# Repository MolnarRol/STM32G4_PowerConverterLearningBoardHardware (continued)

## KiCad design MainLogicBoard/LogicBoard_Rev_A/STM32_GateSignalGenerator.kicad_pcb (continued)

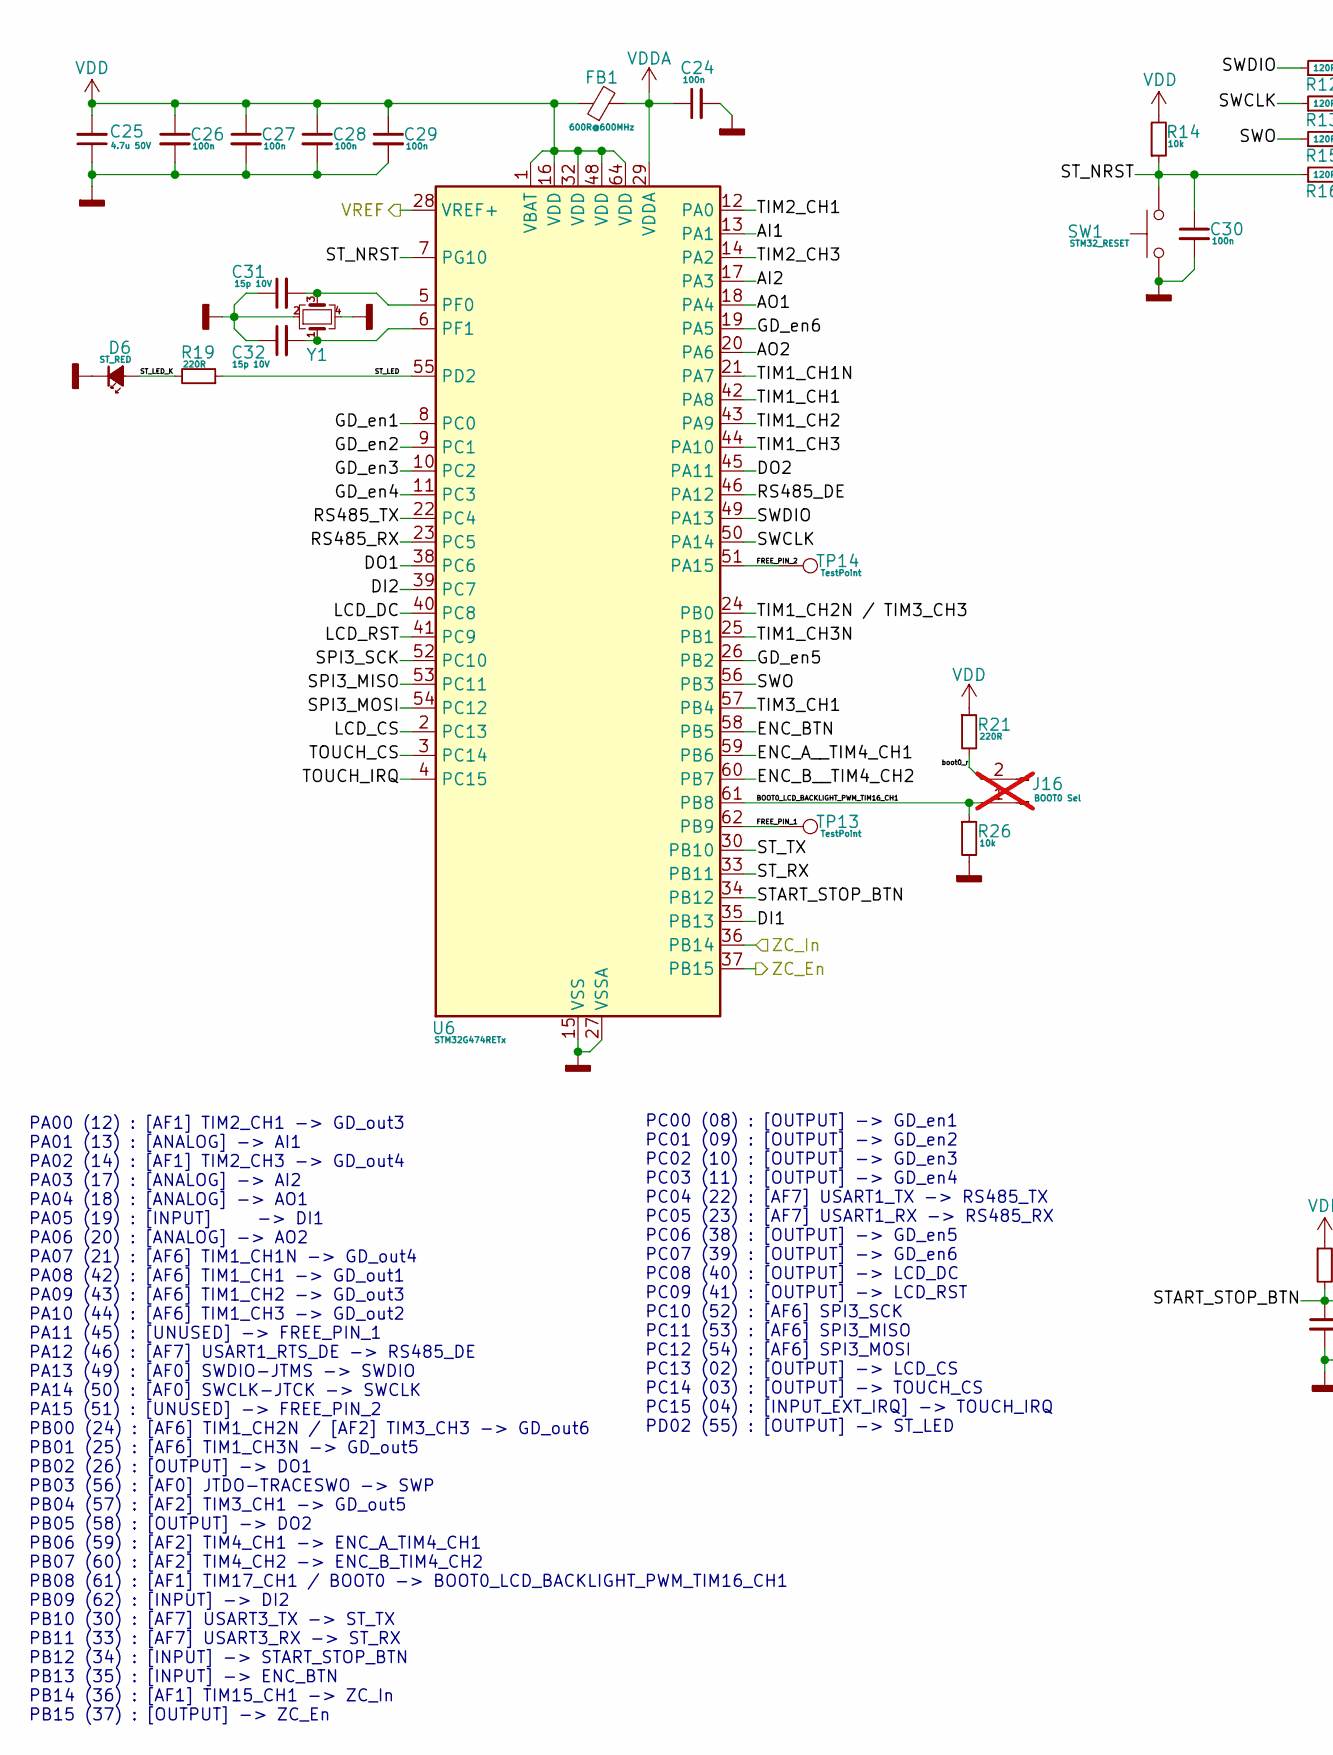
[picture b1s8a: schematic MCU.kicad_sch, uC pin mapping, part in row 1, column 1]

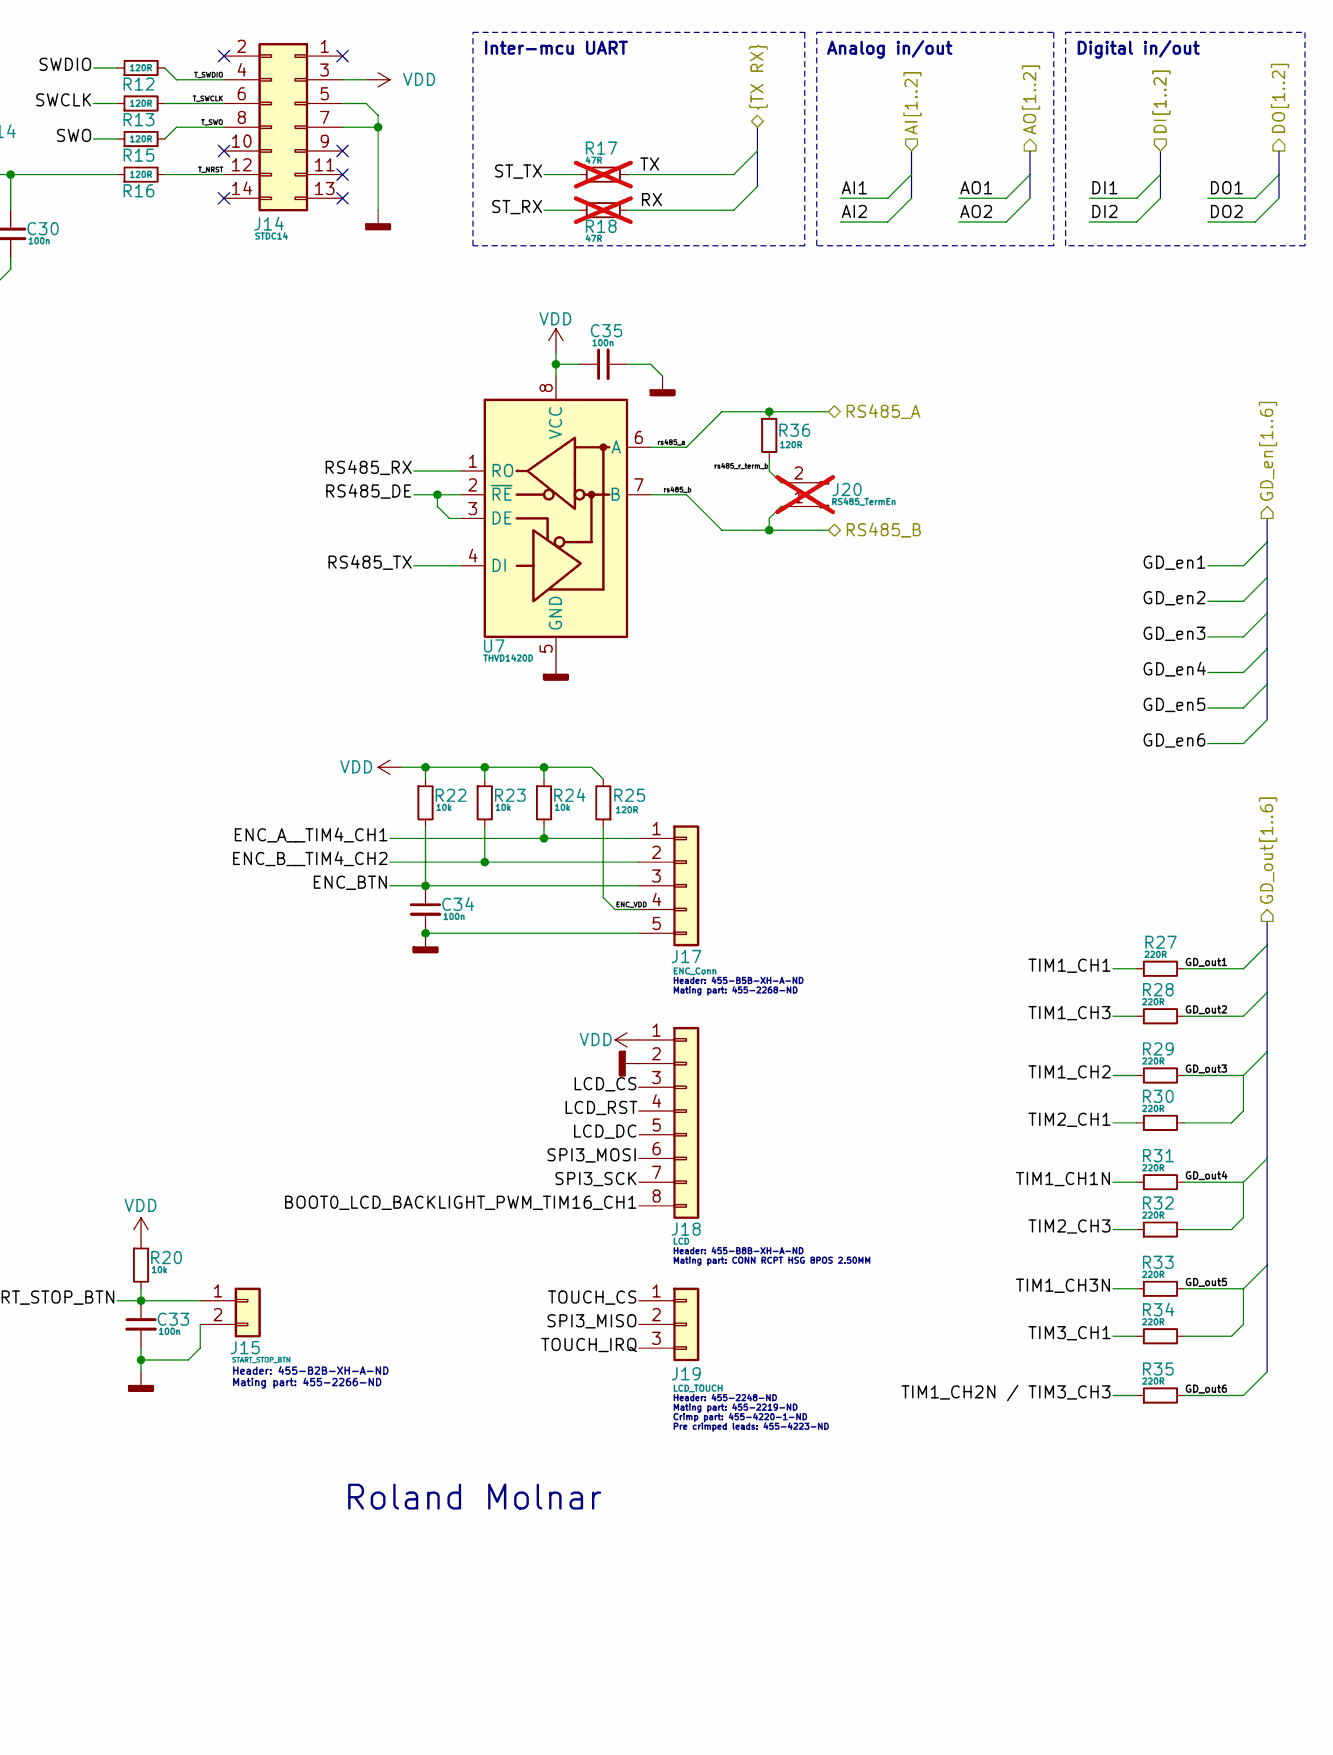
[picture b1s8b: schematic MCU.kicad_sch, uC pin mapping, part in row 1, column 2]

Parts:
C24, C30, C33, C34, C35: 100n; C_0805_2012Metric; Manufacturer PN C0805C104K5RAC7411; DigiKey PN 399-C0805C104K5RAC7210CT-ND
C25: 4.7u 50V; C_1206_3216Metric; Manufacturer PN GRM31CR71H475KA12L; DigiKey PN 490-6521-1-ND
C26, C27, C28, C29: 100n; C_0603_1608Metric; Manufacturer PN 06035C104JAT2A; DigiKey PN 478-KGM15BR71H104JTCT-ND
C31, C32: 15p 10V; C_0603_1608Metric; Manufacturer PN C0603C150M8GACTU; DigiKey PN 399-C0603C150M8GACTUCT-ND
D6: ST_RED; LED_0805_2012Metric; Manufacturer PN LTST-C171KRKT; DigiKey PN 160-1427-1-ND
FB1: 600R@600MHz; R_0805_2012Metric; Manufacturer PN BLM21HE122SN1L; DigiKey PN 490-BLM21HE122SN1LCT-ND
J14: STDC14; SAMTEC_FTSH-107-01-L-DV-K-A; Manufacturer PN SAMTEC_FTSH-107-01-L-DV-K-A; DigiKey PN FTSH-107-01-L-DV-K-A-ND
J15: START_STOP_BTN; JST_XH_B2B-XH-A_1x02_P2.50mm_Vertical; Manufacturer PN B2B-XH-A; DigiKey PN 455-B2B-XH-A-ND
J16: BOOT0 Sel; PinHeader_1x02_P2.54mm_Vertical; not fitted
J17: ENC_Conn; JST_XH_B5B-XH-A_1x05_P2.50mm_Vertical; Manufacturer PN B5B-XH-A; DigiKey PN 455-B5B-XH-A-ND
J18: LCD; JST_XH_B8B-XH-A_1x08_P2.50mm_Vertical; Manufacturer PN B8B-XH-A; DigiKey PN 455-B8B-XH-A-ND
J19: LCD_TOUCH; JST_XH_B3B-XH-A_1x03_P2.50mm_Vertical; Manufacturer PN B3B-XH-A; DigiKey PN 455-2248-ND
J20: RS485_TermEn; PinHeader_1x02_P2.54mm_Vertical; not fitted
R12, R13, R15, R16, R25: 120R; R_0603_1608Metric; Manufacturer PN AC0603FR-07120RL; DigiKey PN YAG3563CT-ND
R14, R20, R22, R23, R24, R26: 10k; R_0805_2012Metric; Manufacturer PN RT0805DRD0710KL; DigiKey PN 311-2699-1-ND
R17, R18: 47R; R_0603_1608Metric; not fitted
R19, R21, R27, R28, R29, R30, R31, R32, R33, R34, R35: 220R; R_0805_2012Metric; Manufacturer PN RC0805FR-07220RL; DigiKey PN 311-220CRCT-ND
R36: 120R; R_0805_2012Metric; Manufacturer PN RC0805FR-07120RL; DigiKey PN 311-120CRCT-ND
SW1: STM32_RESET; SW_SPST_PTS647_Sx38; Manufacturer PN PTS647SN50SMTR2 LFS; DigiKey PN PTS647SN50SMTR2LFSCT-ND
TP13, TP14: TestPoint; TestPoint_Pad_D1.5mm
U6: STM32G474RETx; LQFP-64_10x10mm_P0.5mm; Manufacturer PN STM32G474RET6; DigiKey PN 497-STM32G474RET6-ND
U7: THVD1420D; SOIC-8_3.9x4.9mm_P1.27mm; Manufacturer PN THVD1420DR; DigiKey PN 296-THVD1420DRCT-ND
Y1: FA-128 24.0000MF10Z-W3; Crystal_SMD_SeikoEpson_FA128-4Pin_2.0x1.6mm; Manufacturer PN FA-128 24.0000MF10Z-W3; DigiKey PN SER3678CT-ND

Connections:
/AnalogInterface/AI1: U6.13 (PA1); also elsewhere on the board
/AnalogInterface/AI2: U6.17 (PA3); also elsewhere on the board
/AnalogInterface/AO1: U6.18 (PA4); also elsewhere on the board
/AnalogInterface/AO2: U6.20 (PA6); also elsewhere on the board
/AnalogInterface/VREF: U6.28 (VREF+); also elsewhere on the board
/DigitalInterface/DI1: U6.35 (PB13); also elsewhere on the board
/DigitalInterface/DI2: U6.39 (PC7); also elsewhere on the board
/DigitalInterface/DO1: U6.38 (PC6); also elsewhere on the board
/DigitalInterface/DO2: U6.45 (PA11); also elsewhere on the board
/Gate driver connectors/GD_en1: U6.8 (PC0); also elsewhere on the board
/Gate driver connectors/GD_en2: U6.9 (PC1); also elsewhere on the board
/Gate driver connectors/GD_en3: U6.10 (PC2); also elsewhere on the board
/Gate driver connectors/GD_en4: U6.11 (PC3); also elsewhere on the board
/Gate driver connectors/GD_en5: U6.26 (PB2); also elsewhere on the board
/Gate driver connectors/GD_en6: U6.19 (PA5); also elsewhere on the board
/Gate driver connectors/GD_out1: R27.2; also elsewhere on the board
/Gate driver connectors/GD_out2: R28.2; also elsewhere on the board
/Gate driver connectors/GD_out3: R29.2, R30.2; also elsewhere on the board
/Gate driver connectors/GD_out4: R31.2, R32.2; also elsewhere on the board
/Gate driver connectors/GD_out5: R33.2, R34.2; also elsewhere on the board
/Gate driver connectors/GD_out6: R35.2; also elsewhere on the board
/MCU/BOOT0_LCD_BACKLIGHT_PWM_TIM16_CH1: J16.1, J18.8, R26.1, U6.61 (PB8)
/MCU/ENC_A__TIM4_CH1: J17.1, R24.2, U6.59 (PB6)
/MCU/ENC_BTN: C34.1, J17.3, R22.2, U6.58 (PB5)
/MCU/ENC_B__TIM4_CH2: J17.2, R23.2, U6.60 (PB7)
/MCU/ENC_VDD: J17.4, R25.1
/MCU/FREE_PIN_1: TP13.1, U6.62 (PB9)
/MCU/FREE_PIN_2: TP14.1, U6.51 (PA15)
/MCU/LCD_CS: J18.3, U6.2 (PC13)
/MCU/LCD_DC: J18.5, U6.40 (PC8)
/MCU/LCD_RST: J18.4, U6.41 (PC9)
/MCU/RS485_DE: U6.46 (PA12), U7.2 (~RE), U7.3 (DE)
/MCU/RS485_RX: U6.23 (PC5), U7.1 (RO)
/MCU/RS485_TX: U6.22 (PC4), U7.4 (DI)
/MCU/SPI3_MISO: J19.2, U6.53 (PC11)
/MCU/SPI3_MOSI: J18.6, U6.54 (PC12)
/MCU/SPI3_SCK: J18.7, U6.52 (PC10)
/MCU/START_STOP_BTN: C33.1, J15.1, R20.2, U6.34 (PB12)
/MCU/ST_LED: R19.1, U6.55 (PD2)
/MCU/ST_LED_K: D6.2 (A), R19.2
/MCU/ST_NRST: C30.1, R14.1, R16.1, SW1.2, U6.7 (PG10)
/MCU/ST_RX: R18.1, U6.33 (PB11)
/MCU/ST_TX: R17.1, U6.30 (PB10)
/MCU/SWCLK: R13.1, U6.50 (PA14)
/MCU/SWDIO: R12.1, U6.49 (PA13)
/MCU/SWO: R15.1, U6.56 (PB3)
/MCU/TIM1_CH1: R27.1, U6.42 (PA8)
/MCU/TIM1_CH1N: R31.1, U6.21 (PA7)
/MCU/TIM1_CH2: R29.1, U6.43 (PA9)
/MCU/TIM1_CH2N / TIM3_CH3: R35.1, U6.24 (PB0)
/MCU/TIM1_CH3: R28.1, U6.44 (PA10)
/MCU/TIM1_CH3N: R33.1, U6.25 (PB1)
/MCU/TIM2_CH1: R30.1, U6.12 (PA0)
/MCU/TIM2_CH3: R32.1, U6.14 (PA2)
/MCU/TIM3_CH1: R34.1, U6.57 (PB4)
/MCU/TOUCH_CS: J19.1, U6.3 (PC14)
/MCU/TOUCH_IRQ: J19.3, U6.4 (PC15)
/MCU/T_NRST: J14.12, R16.2
/MCU/T_SWCLK: J14.6, R13.2
/MCU/T_SWDIO: J14.4, R12.2
/MCU/T_SWO: J14.8, R15.2
/MCU/ZC_En: U6.37 (PB15); also elsewhere on the board
/MCU/ZC_In: U6.36 (PB14); also elsewhere on the board
/MCU/boot0_r: J16.2, R21.2
/MCU/rs485_a: R36.1, U7.6 (A); also elsewhere on the board
/MCU/rs485_b: J20.1, U7.7 (B); also elsewhere on the board
/MCU/rs485_r_term_b: J20.2, R36.2
/Uart.RX: R18.2; also elsewhere on the board
/Uart.TX: R17.2; also elsewhere on the board
GNDD: C24.2, C25.1, C26.2, C27.2, C28.2, C29.2, C30.2, C31.1, C32.1, C33.2, C34.2, C35.2, D6.1 (K), J14.5, J14.7, J15.2, J17.5, J18.2, R26.2, SW1.1, U6.15 (VSS), U6.27 (VSSA), U6.31 (VSS), U6.47 (VSS), U6.63 (VSS), U7.5 (GND), Y1.2, Y1.4; also elsewhere on the board
unnamed: C31.2, U6.5 (PF0), Y1.3
unnamed: C32.2, U6.6 (PF1), Y1.1
VDD: C25.2, C26.1, C27.1, C28.1, C29.1, C35.1, FB1.1, J14.3, J18.1, R14.2, R20.1, R21.1, R22.1, R23.1, R24.1, R25.2, U6.1 (VBAT), U6.16 (VDD), U6.32 (VDD), U6.48 (VDD), U6.64 (VDD), U7.8 (VCC); also elsewhere on the board
VDDA: C24.1, FB1.2, U6.29 (VDDA); also elsewhere on the board

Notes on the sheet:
Header: 455-B8B-XH-A-ND Mating part: CONN RCPT HSG 8POS 2.50MM
PA00 (12) : [AF1] TIM2_CH1 -> GD_out3 PA01 (13) : [ANALOG] -> AI1 PA02 (14) : [AF1] TIM2_CH3 -> GD_out4 PA03 (17) : [ANALOG] -> AI2 PA04 (18) : [ANALOG] -> AO1 PA05 (19) : [INPUT] -> DI1 PA06 (20) : [ANALOG] -> AO2 PA07 (21) : [AF6] TIM1_CH1N -> GD_out4 PA08 (42) : [AF6] TIM1_CH1 -> GD_out1 PA09 (4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
Header: 455-B2B-XH-A-ND Mating part: 455-2266-ND
Header: 455-2248-ND Mating part: 455-2219-ND Crimp part: 455-4220-1-ND Pre crimped leads: 455-4223-ND
Header: 455-B5B-XH-A-ND Mating part: 455-2268-ND
Roland Molnar
PC00 (08) : [OUTPUT] -> GD_en1 PC01 (09) : [OUTPUT] -> GD_en2 PC02 (10) : [OUTPUT] -> GD_en3 PC03 (11) : [OUTPUT] -> GD_en4 PC04 (22) : [AF7] USART1_TX -> RS485_TX PC05 (23) : [AF7] USART1_RX -> RS485_RX PC06 (38) : [OUTPUT] -> GD_en5 PC07 (39) : [OUTPUT] -> GD_en6 PC08 (40) : [OUTPUT] -> LCD_DC PC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
Inter-mcu UART
Analog in/out
Digital in/out

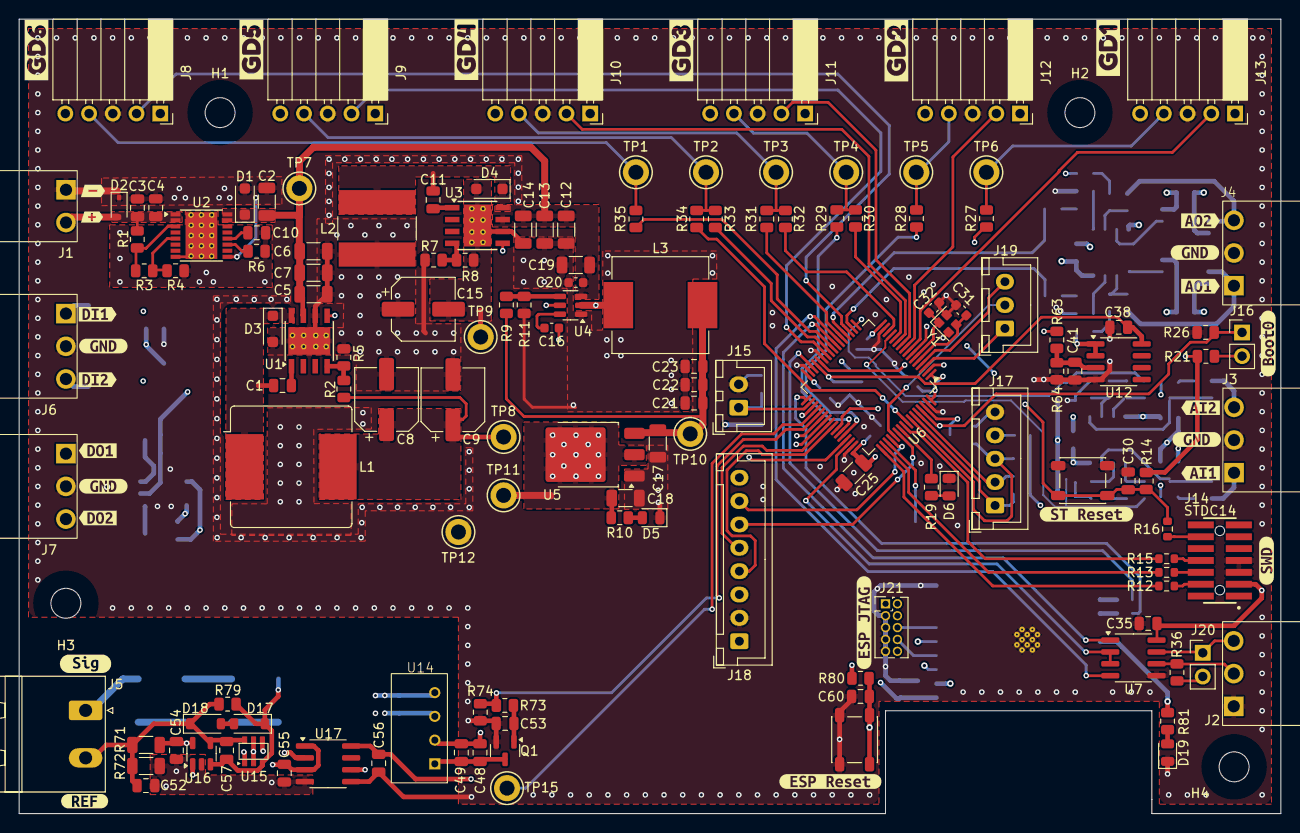
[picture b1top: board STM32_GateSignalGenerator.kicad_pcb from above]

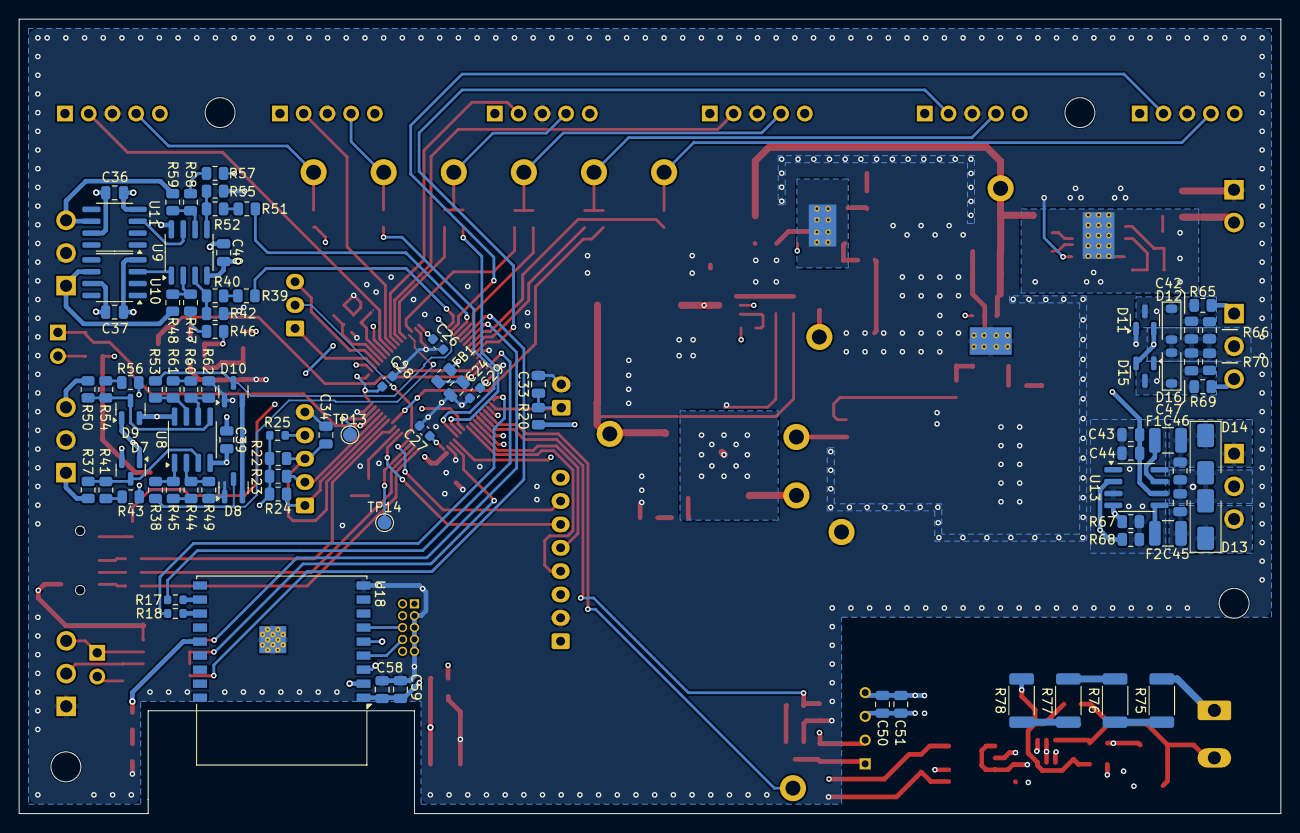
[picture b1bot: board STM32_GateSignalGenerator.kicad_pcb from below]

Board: 4 copper layers, 135.0 x 85.0 mm, 255 parts (85 on the bottom side), 145 nets.

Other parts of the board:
kibuzzard-66B36A2A: G***; kibuzzard-66B36A2A
kibuzzard-66B36A4C: G***; kibuzzard-66B36A4C
kibuzzard-66B36A39: G***; kibuzzard-66B36A39
kibuzzard-66B36A62: G***; kibuzzard-66B36A62
kibuzzard-66B369BA: G***; kibuzzard-66B369BA
kibuzzard-66B369E5: G***; kibuzzard-66B369E5
kibuzzard-677E6BFE: G***; kibuzzard-677E6BFE
kibuzzard-677E6C29: G***; kibuzzard-677E6C29
kibuzzard-678FFDA4: G***; kibuzzard-678FFDA4
kibuzzard-678FFDC4: G***; kibuzzard-678FFDC4
kibuzzard-678FFDE1: G***; kibuzzard-678FFDE1
kibuzzard-678FFE04: G***; kibuzzard-678FFE04
kibuzzard-678FFE4A: G***; kibuzzard-678FFE4A
kibuzzard-678FFE18: G***; kibuzzard-678FFE18
kibuzzard-678FFE25: G***; kibuzzard-678FFE25
kibuzzard-678FFE33: G***; kibuzzard-678FFE33
kibuzzard-678FFE55: G***; kibuzzard-678FFE55
kibuzzard-678FFFB3: G***; kibuzzard-678FFFB3
kibuzzard-678FFFC0: G***; kibuzzard-678FFFC0
kibuzzard-678FFFD0: G***; kibuzzard-678FFFD0
kibuzzard-678FFFDA: G***; kibuzzard-678FFFDA
kibuzzard-678FFFEA: G***; kibuzzard-678FFFEA
kibuzzard-678FFFF4: G***; kibuzzard-678FFFF4
kibuzzard-679001ED: G***; kibuzzard-679001ED
kibuzzard-6790012D: G***; kibuzzard-6790012D
kibuzzard-67900122: G***; kibuzzard-67900122
kibuzzard-67900201: G***; kibuzzard-67900201

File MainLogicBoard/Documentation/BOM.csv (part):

"#","Reference","Manufacturer PN","Mouser PN","DigiKey PN","Qty","Value","Footprint","Description","DNP"
"1","C10","CL21A225KB9LNNC","187-CL21A225KB9LNNC ","1276-2409-1-ND","1","2u7 50V","Capacitor_SMD:C_0805_2012Metric","Unpolarized capacitor, small symbol",""
"2","C19","12065C225K4T2A","581-12065C225K4T2A","478-KAM31GR71H225KUCT-ND","1","2u2 50V","Capacitor_SMD:C_1206_3216Metric","C0805C106K8PACTU",""
"3","C1,C11","KGM21NR71H103KT","581-08055C103K","478-KGM21NR71H103KTCT-ND","2","10n","Capacitor_SMD:C_0805_2012Metric","08055C103KAT2A",""
"4","C16,C20,C26,C27,C28,C29","06035C104JAT2A","581-06035C104JAT2A","478-KGM15BR71H104JTCT-ND","6","100n","Capacitor_SMD:C_0603_1608Metric","-- mixed values --",""
"5","C2,C5,C6,C7,C12,C13,C14,C17,C18,C25","GRM31CR71H475KA12L","81-GRM31CR71H475KA2L","490-6521-1-ND","10","4.7u 50V","Capacitor_SMD:C_1206_3216Metric","GRM31CR71H475KA12L",""
"6","C3,C21,C22,C23,C43,C48,C51,C53,C58","C0805C106K8PACTU","80-C0805C106K8P","399-C0805C106K8PACTUCT-ND","9","10u","Capacitor_SMD:C_0805_2012Metric","-- mixed values --",""
"7","C31,C32","C0603C150M8GACTU","80-C0603C150M8G","399-C0603C150M8GACTUCT-ND","2","15p 10V","Capacitor_SMD:C_0603_1608Metric","C0603C150M8GACTU",""
"8","C4,C24,C30,C33,C34,C35,C36,C37,C38,C39,C40,C41,C44,C49,C50,C52,C54,C55,C56,C59,C60","C0805C104K5RAC7411","80-C0805C104K5RACLR","399-C0805C104K5RAC7210CT-ND","21","100n","Capacitor_SMD:C_0805_2012Metric","Unpolarized capacitor, small symbol",""
"9","C42,C45,C46,C47","C0805C102K5RACTU","80-C0805C102K5R","399-C0805C102K5RACTUCT-ND","4","1n","Capacitor_SMD:C_0805_2012Metric","Unpolarized capacitor, small symbol",""
"10","C8,C9,C15","UUD1E270MCL1GS","647-UUD1E270MCL","493-2271-1-ND","3","27u 25V","Capacitor_SMD:CP_Elec_6.3x5.8","",""
"11","D2","DESD1LIN2WSQ-7"," 621-DESD1LIN2WSQ-7 ","DESD1LIN2WSQ-7DICT-ND","1","TVS","Diode_SMD:D_SOD-323","SOD-323 DESD1LIN2WSQ-7",""
"12","D1,D3,D4","SS24FL"," 512-SS24FL ","SS24FLCT-ND","3","SS24FL","Diode_SMD:D_SOD-123F","SS24FL",""
"13","D13,D14","SMAJ24A","576-SMAJ24A","SMAJ24ALFCT-ND","2","SMAJ24A","Diode_SMD:D_SMA","400W unidirectional Transient Voltage Suppressor, 24.0Vr, SMA(DO-214AC)",""
"14","D17,D18","SZMMSZ4680T1G","863-SZMMSZ4680T1G","SZMMSZ4680T1GOSCT-ND","2","SZMMSZ4680T1G","Diode_SMD:D_SOD-123","Zener diode, small symbol",""
"15","D5,D6,D19","LTST-C171KRKT ","859-LTST-C171KRKT","160-1427-1-ND","3","-- mixed values --","LED_SMD:LED_0805_2012Metric","LED",""
"16","D7,D8,D9,D10,D11,D15","BAT54S","637-BAT54S","4878-BAT54SCT-ND","6","BAT54S","Package_TO_SOT_SMD:SOT-23","Vr 30V, If 200mA, Dual schottky barrier diode, in series, SOT-323",""
"17","F1,F2","MICROSMD010F-2","650-MICROSMD010F-2","MICROSMD010F-2CT-ND","2","250mA Trip 100mA Hold","Fuse:Fuse_1210_3225Metric","MICROSMD010F-2",""
"18","FB1","BLM21HE122SN1L"," 81-BLM21HE122SN1L ","490-BLM21HE122SN1LCT-ND","1","600R@600MHz","Resistor_SMD:R_0805_2012Metric","Ferrite bead, small symbol",""
"19","J1","2350514-2","538-39502-6002","A145378-ND","1","Power in","ProjectLib:TE 2350514-2","Plugable screw terminal 01x02",""
"20","J5","1757242","651-1757242 ","277-1106-ND","1","Zero crossing input","Connector_Phoenix_MSTB:PhoenixContact_MSTBA_2,5_2-G-5,08_1x02_P5.08mm_Horizontal","Generic screw terminal, single row, 01x02, script generated (kicad-library-utils/schlib/autogen/connector/)",""
"21","J14","SAMTEC_FTSH-107-01-L-DV-K-A","200-FTSH10701LDVKA ","FTSH-107-01-L-DV-K-A-ND","1","STDC14","ProjectLib:SAMTEC_FTSH-107-01-L-DV-K-A","ARM debug connector",""
"22","J15","B2B-XH-A","306-B2BXHALFSNP","455-B2B-XH-A-ND","1","START_STOP_BTN","Connector_JST:JST_XH_B2B-XH-A_1x02_P2.50mm_Vertical","Generic connector, single row, 01x02, script generated (kicad-library-utils/schlib/autogen/connector/)",""
"23","J17","B5B-XH-A","306-B5BXHALFSN","455-B5B-XH-A-ND","1","ENC_Conn","Connector_JST:JST_XH_B5B-XH-A_1x05_P2.50mm_Vertical","Generic connector, single row, 01x05, script generated (kicad-library-utils/schlib/autogen/connector/)",""
"24","J18","B8B-XH-A","306-B8BXHALFSNP","455-B8B-XH-A-ND","1","LCD","Connector_JST:JST_XH_B8B-XH-A_1x08_P2.50mm_Vertical","Generic connector, single row, 01x08, script generated (kicad-library-utils/schlib/autogen/connector/)",""
"25","J19","B3B-XH-A","306-B3BXHALFSNP","455-2248-ND","1","LCD_TOUCH","Connector_JST:JST_XH_B3B-XH-A_1x03_P2.50mm_Vertical","Generic connector, single row, 01x03, script generated (kicad-library-utils/schlib/autogen/connector/)",""
"26","J21","FTSH-105-01-L-D-K","200-FTSH10501LDK","SAM8798-ND","1","ESP_JTAG","Connector_PinHeader_1.27mm:PinHeader_2x05_P1.27mm_Vertical","3221-10-0300-00",""
"27","J22","2350398-2","538-39500-5002","A145367-ND","1","Screw_Terminal_01x02","","Generic screw terminal, single row, 01x02, script generated (kicad-library-utils/schlib/autogen/connector/)",""
"28","J28","1757019","651-1757019 ","277-1011-ND","1","Screw_Terminal_01x02","","Generic screw terminal, single row, 01x02, script generated (kicad-library-utils/schlib/autogen/connector/)",""
"29","J2,J3,J4,J6,J7","2350514-3","571-2350514-3","A145379-ND","5","-- mixed values --","ProjectLib:TE 2350514-3","Plugable screw terminal 01x03",""
"30","J23,J24,J25,J26,J27","284506-3","571-2845063","A98374-ND","5","Screw_Terminal_01x03","","Generic screw terminal, single row, 01x03, script generated (kicad-library-utils/schlib/autogen/connector/)",""
"31","J8,J9,J10,J11,J12,J13","SSW-105-02-F-S-RA","200-SSW10502FSRA","612-SSW-105-02-F-S-RA-ND","6","Pin socket 2.54mm 1x5 90 deg","Connector_PinSocket_2.54mm:PinSocket_1x05_P2.54mm_Horizontal","Generic connector, single row, 01x05, script generated",""
"32","L1","SRR1208-470YL","652-SRR1208-470YL","SRR1208-470YLCT-ND","1","47u","Inductor_SMD:L_Bourns_SRR1208_12.7x12.7mm","SRR1208-470YL",""
"33","L2","SDR0805-101KL","652-SDR0805-101KL ","118-SDR0805-101KLCT-ND","1","100u","Inductor_SMD:L_Bourns-SRN8040_8x8.15mm","SDR0805-101KL",""
"34","L3","IHLP4040DZER3R3M01","70-IHLP4040DZER3R3M0 ","541-1298-1-ND","1","3u3","Inductor_SMD:L_Vishay_IHLP-4040","Inductor, small symbol",""
"35","Q1","DMN2056U-7","621-DMN2056U-7","DMN2056U-7DICT-ND","1","DMN2056U","Package_TO_SOT_SMD:SOT-23","0.115A Id, 60V Vds, N-Channel MOSFET, SOT-23",""
"36","R1","RC0805FR-0793K1L","603-RC0805FR-0793K1L","311-93.1KCRCT-ND","1","93k1 1%","Resistor_SMD:R_0805_2012Metric","Resistor, small symbol",""
"37","R3","RC0805FR-071K69L","603-RC0805FR-071K69L ","311-1.69KCRCT-ND","1","1k69 1%","Resistor_SMD:R_0805_2012Metric","Resistor, small symbol",""
"38","R4","RC0805FR-074K22L","603-RC0805FR-074K22L","311-4.22KCRCT-ND","1","4k22 1%","Resistor_SMD:R_0805_2012Metric","Resistor, small symbol",""
"39","R6","RC0805FR-077K87L","603-RC0805FR-077K87L","311-7.87KCRCT-ND","1","7k87 1%","Resistor_SMD:R_0805_2012Metric","Resistor, small symbol",""
"40","R9","RC0805FR-07162KL","603-RC0805FR-07162KL","311-162KCRCT-ND","1","162k","Resistor_SMD:R_0805_2012Metric","Resistor, small symbol",""
"41","R11","RC0805FR-0722K1L","603-RC0805FR-0722K1L","311-22.1KCRCT-ND","1","22k1","Resistor_SMD:R_0805_2012Metric","Resistor, small symbol",""
"42","R10,R19,R21,R27,R28,R29,R30,R31,R32,R33,R34,R35,R81","RC0805FR-07220RL","603-RC0805FR-07220RL","311-220CRCT-ND","13","220R","Resistor_SMD:R_0805_2012Metric","Resistor, small symbol",""
"43","R12,R13,R15,R16,R25","AC0603FR-07120RL","603-AC0603FR-07120RL","YAG3563CT-ND","5","120R","Resistor_SMD:R_0603_1608Metric","Resistor, small symbol",""
"44","R2,R7,R14,R20,R22,R23,R24,R26,R37,R42,R48,R49,R50,R55,R59,R62,R67,R68,R74,R80","RT0805DRD0710KL","603-RT0805DRD0710KL ","311-2699-1-ND","20","-- mixed values --","Resistor_SMD:R_0805_2012Metric","-- mixed values --",""
"45","R36,R38,R53","RC0805FR-07120RL","603-RC0805FR-07120RL","311-120CRCT-ND","3","120R","Resistor_SMD:R_0805_2012Metric","Resistor, small symbol",""
"46","R39,R41,R45,R47,R51,R54,R58,R61","ERJ-PB6D5600V","667-ERJ-PB6D5600V","P20990CT-ND","8","560R 0.5%","Resistor_SMD:R_0805_2012Metric","Resistor, small symbol",""
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
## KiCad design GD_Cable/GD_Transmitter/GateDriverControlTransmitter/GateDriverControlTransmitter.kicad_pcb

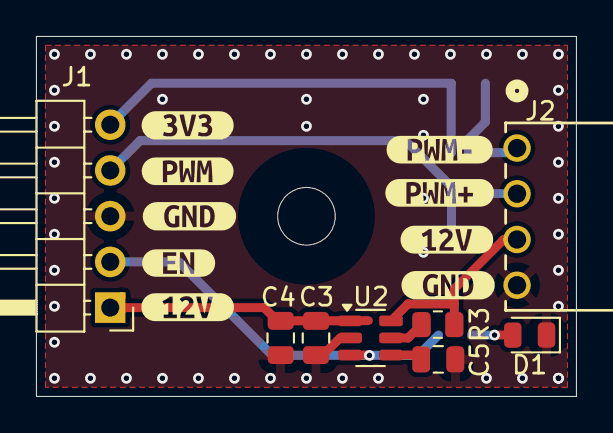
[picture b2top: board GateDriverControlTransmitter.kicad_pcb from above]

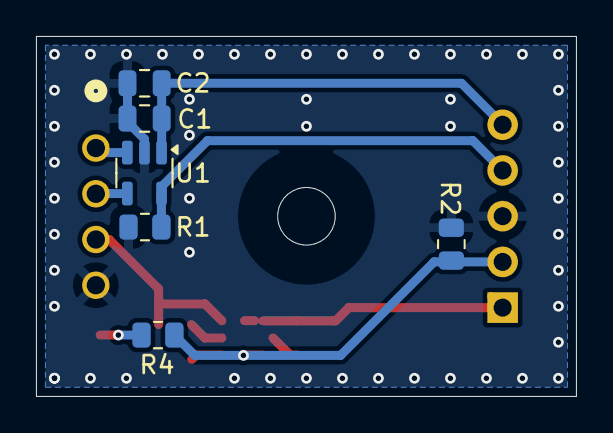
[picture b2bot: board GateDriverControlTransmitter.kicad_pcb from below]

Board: 2 copper layers, 30.0 x 20.0 mm, 24 parts (6 on the bottom side), 11 nets.

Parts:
C1, C3: 100n; C_0805_2012Metric
C2, C4: 1u; C_0805_2012Metric
C5: 6u8; C_0805_2012Metric
D1: Red on; LED_0805_2012Metric
H1: M3; MountingHole_3.2mm_M3
J1: GD transmitter input; PinHeader_1x05_P2.54mm_Horizontal
J2: GD_Cable; 640457-4_TYC
R1, R2: 10k; R_0805_2012Metric
R3, R4: 220R; R_0805_2012Metric
U1: DS90LV011A; SOT-23-5
U2: TPS22810DBRV; SOT-23-6
kibuzzard-679273A0: G***; kibuzzard-679273A0
kibuzzard-679273B0: G***; kibuzzard-679273B0
kibuzzard-679273BE: G***; kibuzzard-679273BE
kibuzzard-679273CA: G***; kibuzzard-679273CA
kibuzzard-679273E3: G***; kibuzzard-679273E3
kibuzzard-679274A7: G***; kibuzzard-679274A7
kibuzzard-679274B3: G***; kibuzzard-679274B3
kibuzzard-679274BF: G***; kibuzzard-679274BF
kibuzzard-67927495: G***; kibuzzard-67927495

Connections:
+3V3: C1.1, C2.1, J1.5, U1.1 (VDD)
+12V: C3.1, C4.1, J1.1, U2.1 (VIN)
/GD_control_signal: J1.4, R1.1, U1.5 (IN)
/GD_enable: J1.2, R2.1, R4.1, U2.3 (EN/UVLO)
/PWM+: J2.2, U1.4 (OUT+)
/PWM-: J2.1, U1.3 (OUT-)
/en_sw_out: J2.3, R3.2, U2.6 (VOUT)
/en_sw_qod: R3.1, U2.5 (QOD)
/led_k: D1.2 (A), R4.2
GNDD: C1.2, C2.2, C3.2, C4.2, C5.2, D1.1 (K), J1.3, J2.4, R1.2, R2.2, U1.2 (GND), U2.2 (GND)
unnamed: C5.1, U2.4 (CT)

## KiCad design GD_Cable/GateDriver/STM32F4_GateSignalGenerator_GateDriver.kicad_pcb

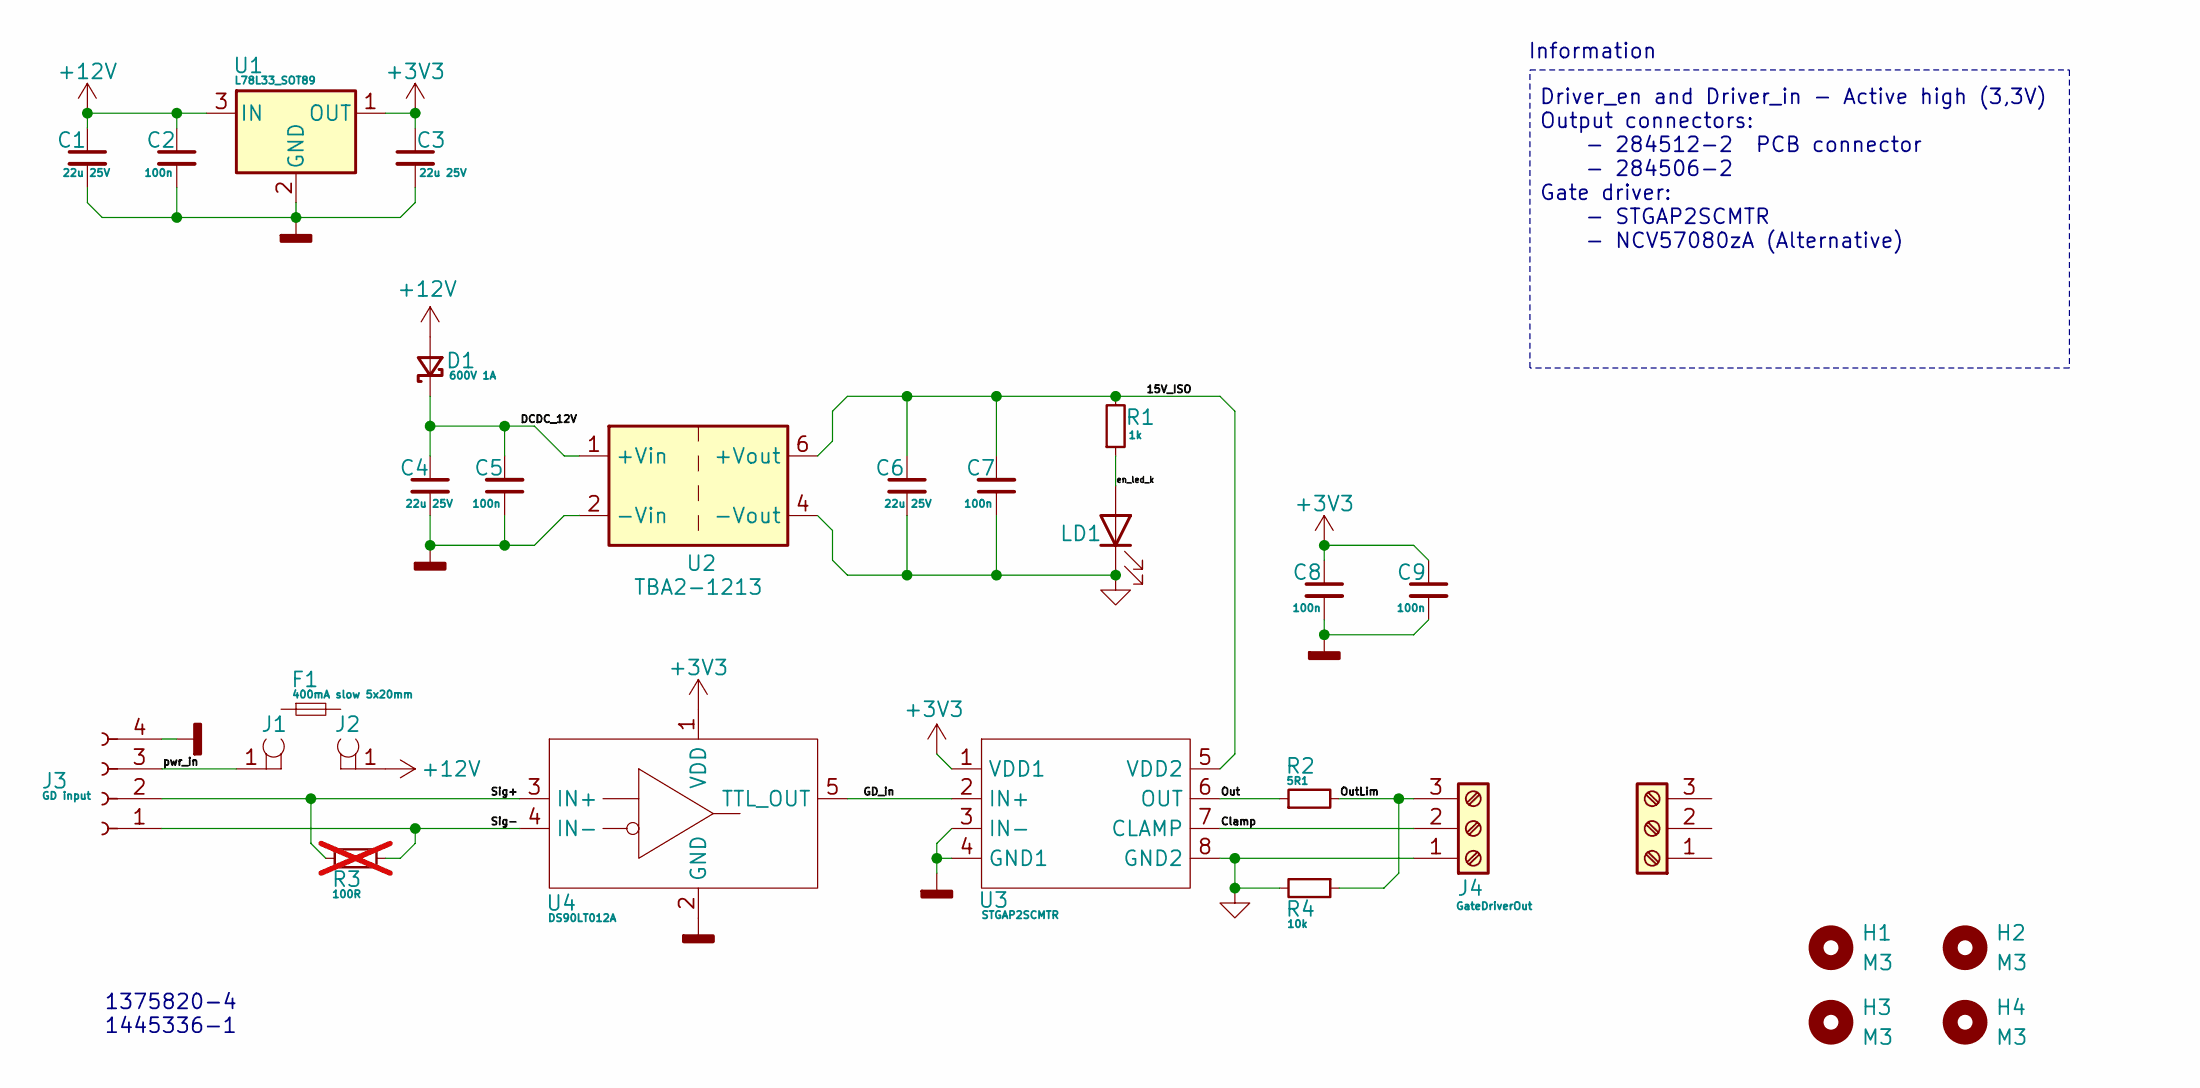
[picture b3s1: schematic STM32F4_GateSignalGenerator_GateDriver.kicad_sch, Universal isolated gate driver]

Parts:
C1, C4, C6: 22u 25V; C_0805_2012Metric; MPN GRM21BR61E226ME44L; DigiKey PN 490-10749-1-ND
C2, C5, C7, C8, C9: 100n; C_0805_2012Metric; MPN C0805C104K5RAC7411; DigiKey PN 399-C0805C104K5RAC7210CT-ND
C3: 22u 25V; C_0805_2012Metric; MPN C0805C104K5RAC7411; DigiKey PN 399-C0805C104K5RAC7210CT-ND
D1: 600V 1A; D_SMA; MPN S1J-13-F; DigiKey PN S1J-FDICT-ND
F1: 400mA slow 5x20mm; MPN 0034.3113; DigiKey PN 486-1216-ND
H1, H2, H3, H4: M3; MountingHole_3.2mm_M3
J1, J2: Fuse holder 5mm; FUSE_3621; MPN 3621; DigiKey PN 36-3621-ND
J3: GD input; 640457-4_TYC; MPN 640457-4; DigiKey PN A1927-ND
J4: GateDriverOut; TE 2350514-3; MPN 2350514-3; DigiKey PN A145379-ND
J5: Screw_Terminal_01x03; Manufacturer PN 284506-3; DigiKey PN A98374-ND
LD1: LED; LED_0805_2012Metric; MPN LTST-C171KRKT; DigiKey PN 160-1427-1-ND
R1: 1k; R_1210_3225Metric; MPN RC1210FR-071KL; DigiKey PN YAG2296CT-ND
R2: 5R1; R_1210_3225Metric; MPN RC1210FR-075R1L; DigiKey PN 13-RC1210FR-075R1LCT-ND
R3: 100R; R_0805_2012Metric; MPN RC0805FR-07100RL; DigiKey PN RC0805FR-07100RL; not fitted
R4: 10k; R_0805_2012Metric; MPN RT0805DRD0710KL; DigiKey PN 311-2699-1-ND
U1: L78L33_SOT89; SOT-89-3; MPN L78L33ABUTR; DigiKey PN 497-7286-1-ND
U2: TBA2-1213; Converter_DCDC_TRACO_TBA2-xxxx_Single_THT; MPN TBA 2-1213; DigiKey PN 1951-3437-ND
U3: STGAP2SCMTR; SOIC-8_3.9x4.9mm_P1.27mm; MPN STGAP2SCMTR; DigiKey PN 497-18116-1-ND
U4: DS90LT012A; SOT-23-5; MPN DS90LT012ATMF/NOPB; DigiKey PN DS90LT012ATMF/NOPBCT-ND

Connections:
+3V3: C3.1, C8.1, C9.1, U1.1 (OUT), U3.1 (VDD1), U4.1 (VDD)
+12V: C1.1, C2.1, D1.2 (A), J2.1, J2.2, U1.3 (IN)
/15V_ISO: C6.1, C7.2, R1.2, U2.6 (+Vout), U3.5 (VDD2)
/Clamp: J4.2, U3.7 (CLAMP)
/DCDC_12V: C4.1, C5.2, D1.1 (K), U2.1 (+Vin)
/GD_in: U3.2 (IN+), U4.5 (TTL_OUT)
/Out: R2.1, U3.6 (OUT)
/OutLim: J4.3, R2.2, R4.1
/Sig+: J3.2, R3.1, U4.3 (IN+)
/Sig-: J3.1, R3.2, U4.4 (IN-)
/en_led_k: LD1.2 (A), R1.1
/pwr_in: J1.1, J1.2, J3.3
GND: C6.2, C7.1, J4.1, LD1.1 (K), R4.2, U2.4 (-Vout), U3.8 (GND2)
GNDD: C1.2, C2.2, C3.2, C4.2, C5.1, C8.2, C9.2, J3.4, U1.2 (GND), U2.2 (-Vin), U3.3 (IN-), U3.4 (GND1), U4.2 (GND)

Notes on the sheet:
1445336-1
Information
1375820-4
Driver_en and Driver_in - Active high (3,3V) Output connectors: - 284512-2 PCB connector - 284506-2 Gate driver: - STGAP2SCMTR - NCV57080zA (Alternative)

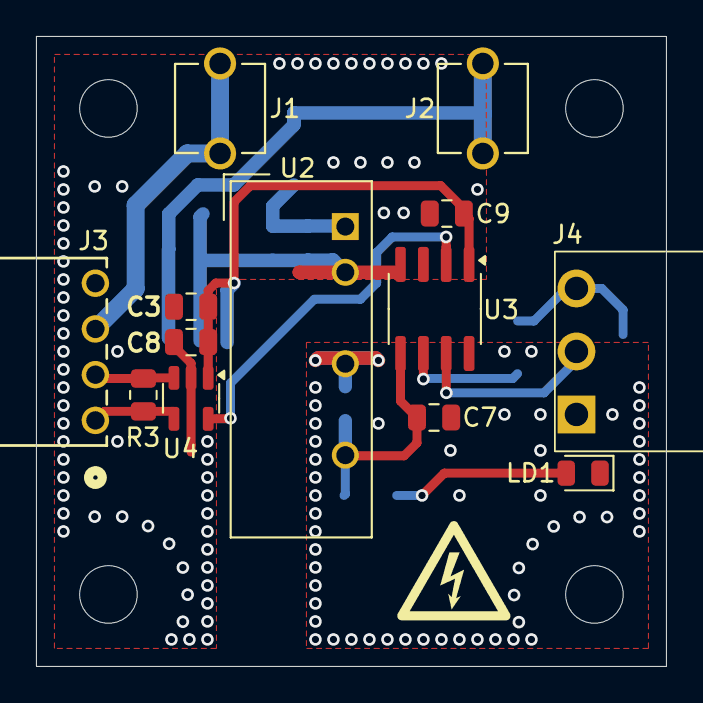
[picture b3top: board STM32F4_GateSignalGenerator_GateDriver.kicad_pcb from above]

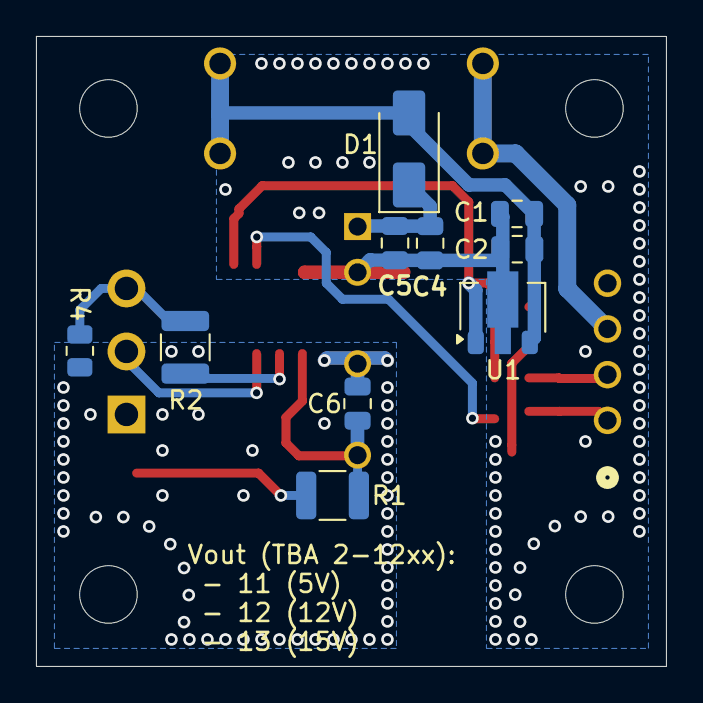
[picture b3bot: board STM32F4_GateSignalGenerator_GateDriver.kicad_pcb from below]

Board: 2 copper layers, 35.0 x 35.0 mm, 27 parts (10 on the bottom side), 14 nets.

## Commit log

2025-03-11 Added project PCBs
